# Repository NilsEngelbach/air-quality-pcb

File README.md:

# Air Quality Checker — PCB

Custom 2-layer KiCad boards for the [air-quality-checker](../air-quality-checker) firmware: a battery-powered
indoor air-quality monitor. A Bosch **BME688** measures the air, an **SG92R** micro servo points at the current IAQ
band, and readings can be uploaded over WiFi. A LiPo cell powers it and charges over USB-C. The device sleeps
~98 % of the time and wakes every 5 minutes.

The repo holds every board revision in its own folder. **The current board is [`v9/`](v9/) (rev I).**

---

## Current board — v9 (rev I)

| Block | Part | Notes |
|---|---|---|
| MCU | **ESP32-C3-WROOM-02-N4** | native USB Serial/JTAG (no USB-UART bridge), antenna in a board notch with no copper beside it |
| Sensor | **BME688** on-board, I²C 0x76 | on a slotted island at the board edge for thermal isolation |
| Indicator | **SG92R** servo header | from VSYS through a load switch (Q6): 0 µA in sleep, 4.5 V on USB / 3.0–4.2 V on battery |
| Charger | **MCP73831**, ~303 mA | charge status to the MCU (IO20) and a green side-view LED |
| Regulator | **AP2112K-3.3** | 600 mA LDO |
| Power path | DMG2305UX P-FETs + B5819W | USB priority, battery reverse-polarity protection, POWER switch drives a FET |
| Controls | POWER (SPDT) + **WiFi mode** (SP3T: OFF / SPARSE / CONTINUOUS) slide switches | right-angle, actuators through the enclosure wall |
| Indicators | blue STATUS + green CHG side-view LEDs | visible from the enclosure side |
| Expansion | **STEMMA QT / Qwiic** port | switched 3.3 V and bus isolation: 0 µA when off; e.g. for a real CO₂ sensor |
| Protection | 2 × USBLC6-2SC6 | USB data lines and the STEMMA QT port |
| Board | Ø 72 mm round, bottom flat for the controls, 2 layers, 1.6 mm FR4 | 0.3 mm minimum drill; assembled by PCBWay |

**State (2026-10-08):** layout done, ERC 0 / DRC 0 with schematic parity; schematic PDF and PCBWay BOM generated.
Gerbers, the ESP32-C3 firmware port and bench validation are still open.

| v9 document | For |
|---|---|
| [`v9/README.md`](v9/README.md) | changes vs v8, pin map, power architecture, firmware port, outputs, next steps |
| [`v9/user-documentation.md`](v9/user-documentation.md) | people using the device |
| [`v9/design_review.md`](v9/design_review.md) | findings F1–F34 with evidence and validation checklists |
| [`v9/layout_constraints.md`](v9/layout_constraints.md) | layout rules |
| [`v9/power_budget.md`](v9/power_budget.md) | sleep floor, wake budget, battery life per WiFi mode |

---

## Revisions

| Rev | Folder | Summary | Docs |
|---|---|---|---|
| A | [`v1/`](v1/) | 108 × 108 mm square. ESP-12F (ESP8266) + CP2102N, BME688 breakout over STEMMA QT, servo from VBAT | [README](v1/README.md) |
| B | [`v2/`](v2/) | Same circuit on a **Ø 72 mm round** board, mounting holes, wind logo | [README](v2/README.md) |
| C | [`v3/`](v3/) | **BME688 soldered on-board**, copper keep-out under the sensor | [README](v3/README.md) |
| D | [`v4/`](v4/) | GPIO2 status LED, battery sensing, USB ESD, battery reverse-polarity FET, spare-GPIO header, fiducials, **5 V servo boost** | [README](v4/README.md) |
| E | [`v5/`](v5/) | Production / assembly refresh (PCBWay BOM, replacement power switch); battery-life analysis | [power budget](v5/power_budget.md) |
| F | [`v6/`](v6/) | Gated servo boost, **3-position WiFi mode switch**, side-view status LED, MΩ battery divider | [README](v6/README.md), [user docs](v6/user-documentation.md), [power budget](v6/power_budget.md) |
| G | [`v7/`](v7/) | **ESP32-C3** (native USB, no CP2102N), FET-driven power switch, servo-rail load switch, long-actuator edge switches, STEMMA QT port, charge-status input, antenna notch and sensor island | [README](v7/README.md), [design review](v7/design_review.md) |
| H | [`v8/`](v8/) | **Servo boost removed** (servo from VSYS), Espressif WROOM-02 footprint so the board keeps the 0.3 mm minimum drill. Fabrication outputs were generated | [README](v8/README.md), [design review](v8/design_review.md) |
| I | [`v9/`](v9/) | Re-placed and re-routed v8: **GPIO remap**, LDO at the module, smaller sensor island, no copper beside the antenna, C24 on the STEMMA QT rail | [README](v9/README.md) and the documents above |

Each revision's README lists what changed against the one before. From v7 on, the design reviews number their
findings (F1, F2, …) and carry them forward, so a finding keeps its number across revisions.

---

## Repository layout

```
README.md                   this overview
build_pcbway_bom.py         KiCad BOM export → PCBWay BOM (python build_pcbway_bom.py v9)
a-sample-of-PCBWay-BOM.xlsx PCBWay's BOM template, the format the script produces
wind.svg                    wind logo used on the back silkscreen (v2+)
vN/
  air-quality-pcb-vN.kicad_pro / .kicad_sch / .kicad_pcb
  README.md, design_review.md, layout_constraints.md, power_budget.md, user-documentation.md   (as available)
  bom_kicad_raw.csv → bom_pcbway_vN.csv, schematic_vN.pdf                                       (as generated)
  Espressif.pretty/, SamacSys_Parts.pretty/, fp-lib-table, air-quality-pcb-vN.3dshapes/       (v7+: vendor footprints and STEP models)
```

Not in git (see `.gitignore`): `gerbers/`, `*.rpt` (ERC/DRC reports), KiCad backups and lock files. Regenerate
them with the `kicad-cli` commands in each revision's README (KiCad 10).

### PCBWay BOM

1. Export the schematic BOM ungrouped, with the fields `Reference,Value,Footprint,Manufacturer,MPN,Description`, to
   `vN/bom_kicad_raw.csv` (command in the revision README).
2. `python build_pcbway_bom.py vN` groups it into PCBWay's columns and writes `vN/bom_pcbway_vN.csv`.

---

## Firmware

The firmware lives in the sibling [`air-quality-checker`](../air-quality-checker) repo. It currently targets the
**ESP8266 boards (v1–v6)**. The ESP32-C3 boards (v7–v9) need a port: PlatformIO `espressif32`, ESP-IDF deep sleep,
the new pin map, BME688 at 0x76. The steps are in [`v7/README.md`](v7/README.md#firmware-port-air-quality-checker-repo),
with the servo rules from v8 and the **v9 pin map** in [`v9/README.md`](v9/README.md#firmware-port-air-quality-checker-repo).
The v7/v8 and v9 pin maps differ, so a v8 build must not be flashed onto a v9 board.

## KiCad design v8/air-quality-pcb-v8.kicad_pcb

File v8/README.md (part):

# Air Quality Checker — PCB v8 (rev H)

Eighth iteration, derived from the routed v7 board. Two changes: the **5 V servo boost is
gone** (the servo now runs from VSYS through the existing load switch), and the **board keeps
PCBWay's standard 0.3 mm minimum drill**: the ESP32-C3-WROOM-02 now uses Espressif's footprint, whose EPAD has no drills.

**State (2026-10-05): layout done, fabrication outputs exported.** Schematic ERC **0 errors / 0 warnings**
(`erc_v8.rpt`). Board DRC with schematic parity **0 errors, 0 unconnected** (`drc_v8.rpt`, also clean after a
zone refill); the only remaining warnings are 4 excluded silkscreen-clipped warnings (U1 at the antenna notch, J1 at the
bottom flat) and the 7 board-only footprints (H1–H4, FID1–3). Gerbers, drill, position file and the PCBWay
BOM are generated (see *Files*). What is left is the order itself and the bench validation. Rules:
[`layout_constraints.md`](layout_constraints.md); findings and validation checklists:
[`design_review.md`](design_review.md) (F1–F24 from v7, F25–F26 new).

For the v6 → v7 changes (ESP32-C3, CP2102N removal, switches, STEMMA QT, …) see [`../v7/README.md`](../v7/README.md).

---

## What changed vs v7

| # | Change | Why (finding) |
|---|---|---|
| 1 | **Boost removed:** U7 MT3608, L1 10 µH, D4 PMEG4030ER, C18 / C21 22 µF, R22 / R23 (feedback) | fewer parts; the servo runs from VSYS (F25) |
| 2 | **Servo rail = VSYS through Q6**: net `SERVO_PWR` (was BOOST_IN + SERVO_5V) = Q6 drain, C22, C19 22 µF, C13 100 µF, J3.2 | servo works on USB (≈ 4.5 V) and on battery (3.0–4.2 V); still 0 µA in sleep (F2, F25) |
| 3 | Nets renamed: **BOOST_EN → SERVO_EN** (IO10), BOOST_GATE → SERVO_GATE, BOOST_PD → SERVO_PD | no boost any more |
| 4 | **U1 footprint → `Espressif:ESP32-C3-WROOM-02`** (from [espressif/kicad-libraries](https://github.com/espressif/kicad-libraries), with STEP): EPAD = 9 pads, no drills | the stock footprint has 12 × 0.2 mm EPAD drills (F15, F26) |
| 5 | **4 GND vias 0.6 / 0.3 mm** in the EPAD gaps (tented); `min_through_hole_diameter` back to **0.3 mm** | PCBWay standard drill (F26) |
| 6 | Board rule area **ANTENNA_KEEPOUT** (28 × 11 mm, F.Cu + B.Cu) | Espressif's footprint only keeps out 18 × 6 mm; this keeps the stock footprint's larger keepout (F7, F26) |
| 7 | Net class **Power**: `/SERVO_5V` → `/SERVO_PWR`, `/BOOST_SW` dropped | (F5) |
| 8 | Title block / back silkscreen **rev H** | |
| 9 | **C19 moved** to (79.5, 49.5) next to C13/J3; SERVO_PWR runs Q6 → C22 → C19 → C13 → J3.2 on F.Cu, 0.8 mm, 25 mm | the boost output position no longer made sense (F25) |
| 10 | **GND stitching near the antenna:** a 15-via fence along the module's ground edge (y 27.5), a ~2.5 mm grid under the module, and vias on both sides of the antenna notch (the left side now has F.Cu pour) | Espressif layout guide: dense GND vias at the module and the antenna (F7) |
| 11 | Silkscreen pin labels **S / + / −** at the servo header J3 | J4 (LiPo) has none: the JST PH plug is keyed |

Everything else (power path, charger, LDO, STEMMA QT, switches, LEDs, outline, placement) is unchanged from v7.

## Pin map (ESP32-C3-WROOM-02)

| GPIO | Net | Function |
|---|---|---|
| IO0 | VBAT_SENSE | ADC1_CH0, divider 1 M / 270 k (4.2 V → 0.89 V, use 2.5 dB attenuation) |
| IO1 | VBUS_SENSE | ADC1_CH1, 5 V → 1.59 V (USB present) |
| IO2 | QT_PWR_N | **STEMMA QT power, active low** (strap pin, R2 10 k pull-up → port off at reset and in sleep) |
| IO3 | MODE_A | SW4 POS1 → LOW = WiFi **OFF** |
| IO4 | MODE_B | SW4 POS3 → LOW = **CONTINUOUS** (both HIGH = SPARSE) |
| IO5 | SERVO_PWM | servo signal via R17 |
| IO6 / IO7 | SDA / SCL | I²C: BME688 (**0x76**) + STEMMA QT port (through Q9/Q10) |
| IO8 | STATUS_LED_N | blue side LED D3, **active-low**; strap (10 k pull-up) |
| IO9 | BOOT | SW2, strap (10 k pull-up) |
| IO10 | **SERVO_EN** | HIGH = servo rail on (Q7 → Q6); R4 100 k pull-down keeps it off |
| IO18 / IO19 | USB D− / D+ | native USB Serial/JTAG |
| IO20 | CHG_DET | charger STAT via divider: LOW = charging (only valid with VBUS present), HIGH = done |
| IO21 | — | not connected (spare) |

## Power architecture

```
USB-C VBUS ─┬─► MCP73831 (303 mA) ─► VBAT_RAW ◄── Q4 (reverse-polarity) ◄── LiPo J4
            │        └─ STAT ─► D2 (green) / R31-R32 ─► IO20
            │                        │
            │                  Q5 (SW3 drives the gate)
            │                        ▼
            └─►|D1|──► VSYS ◄── Q3 (USB priority) ── VBAT
                        │
                        ├─► AP2112K-3.3 ─► +3V3 (ESP32-C3, BME688, LED) ─► Q8 (IO2) ─► QT_3V3 ─► J5
                        └─► Q6 (SERVO_EN via Q7) ─► SERVO_PWR (C19 22 µF + C13 100 µF) ─► J3
```

Servo supply: **≈ 4.5 V on USB** (VBUS − D1), **3.0–4.2 V on battery**. The SG92R is rated 4.8–6 V; on
battery it moves with less torque and speed (F25 — validate on the bench).

Sleep floor estimate unchanged: ≈ **66 µA** (ESP32-C3 5 µA + AP2112K 55 µA + VBAT divider 3.3 µA +
BME688 ~2 µA + R26 0.4 µA; servo rail and QT port 0). Measure before updating the battery tables.

## Firmware port (air-quality-checker repo)

As in [`../v7/README.md`](../v7/README.md#firmware-port-air-quality-checker-repo), with these servo changes:

- **IO10 is now `SERVO_EN`** (was BOOST_EN): drive it HIGH **≥ 50 ms before** a move (SERVO_PWR ramps at
  ~0.5 V/ms, ≈ 8 ms to VSYS), LOW again after the move and before deep sleep.
- **Skip or postpone servo moves when VBAT < ~3.5 V** on battery: the servo's start-up current can pull VSYS
  below the LDO's dropout and brown out the ESP32-C3 (F25).
- **Prefer moving the servo with WiFi off** (not during TX bursts). On a 500 mA USB 2.0 port, charger + WiFi + servo
  start can exceed the port budget.
- Never drive SERVO_PWM while SERVO_EN is LOW (it would back-feed the unpowered servo through R17).

## Files

| File | Purpose |
|---|---|
| `air-quality-pcb-v8.kicad_pro/.kicad_sch/.kicad_pcb` | v8 project (ERC clean; board DRC clean with parity) |
| `Espressif.pretty/`, `SamacSys_Parts.pretty/`, `fp-lib-table` | vendor footprints: U1 (Espressif) and SW4 (OS103011MA7QP1, Mouser / SamacSys) |
| `air-quality-pcb-v8.3dshapes/` | STEP models for the vendor footprints and the side LEDs |
| `design_review.md` | findings F1–F26 with evidence, sources and validation checklists |
| `layout_plan.md` | what changed on the board, and the remaining layout steps for v8 |
| `layout_constraints.md` | the rules: antenna, servo rail, edge overhang, widths |
| `schematic_v8.pdf` | plotted schematic |
| `erc_v8.rpt` / `drc_v8.rpt` | ERC (clean) / DRC with schematic parity (clean) |
| `gerbers/air-quality-pcb-v8-gerbers.zip` | **upload to PCBWay:** 9 Gerber layers + job file + drill file (Excellon, PTH and NPTH merged; smallest hole 0.30 mm) |
| `gerbers/` | the same files unzipped, plus `air-quality-pcb-v8-drl_map.pdf` and `air-quality-pcb-v8-pos.csv` (placement, mm, all top side: 71 parts + 3 fiducials) |
| `bom_kicad_raw.csv` → `bom_pcbway_v8.csv` | schematic BOM export → PCBWay BOM (38 lines, 71 placements; SW3, SW4, J3, J4 THT), built with `python build_pcbway_bom.py v8` |

### Regenerate outputs (run in `v8/`)

```sh
kicad-cli sch erc -o erc_v8.rpt air-quality-pcb-v8.kicad_sch
kicad-cli pcb drc --schematic-parity -o drc_v8.rpt air-quality-pcb-v8.kicad_pcb
kicad-cli pcb export gerbers -o gerbers/ --subtract-soldermask --check-zones \
  --layers "F.Cu,B.Cu,F.Paste,B.Paste,F.Silkscreen,B.Silkscreen,F.Mask,B.Mask,Edge.Cuts" air-quality-pcb-v8.kicad_pcb
kicad-cli pcb export drill -o gerbers/ --format excellon --generate-map --map-format pdf air-quality-pcb-v8.kicad_pcb
kicad-cli pcb export pos -o gerbers/air-quality-pcb-v8-pos.csv --format csv --units mm --side both air-quality-pcb-v8.kicad_pcb
kicad-cli sch export bom -o bom_kicad_raw.csv --fields "Reference,Value,Footprint,Manufacturer,MPN,Description" \
  --group-by "" air-quality-pcb-v8.kicad_sch
python ../build_pcbway_bom.py v8
```

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
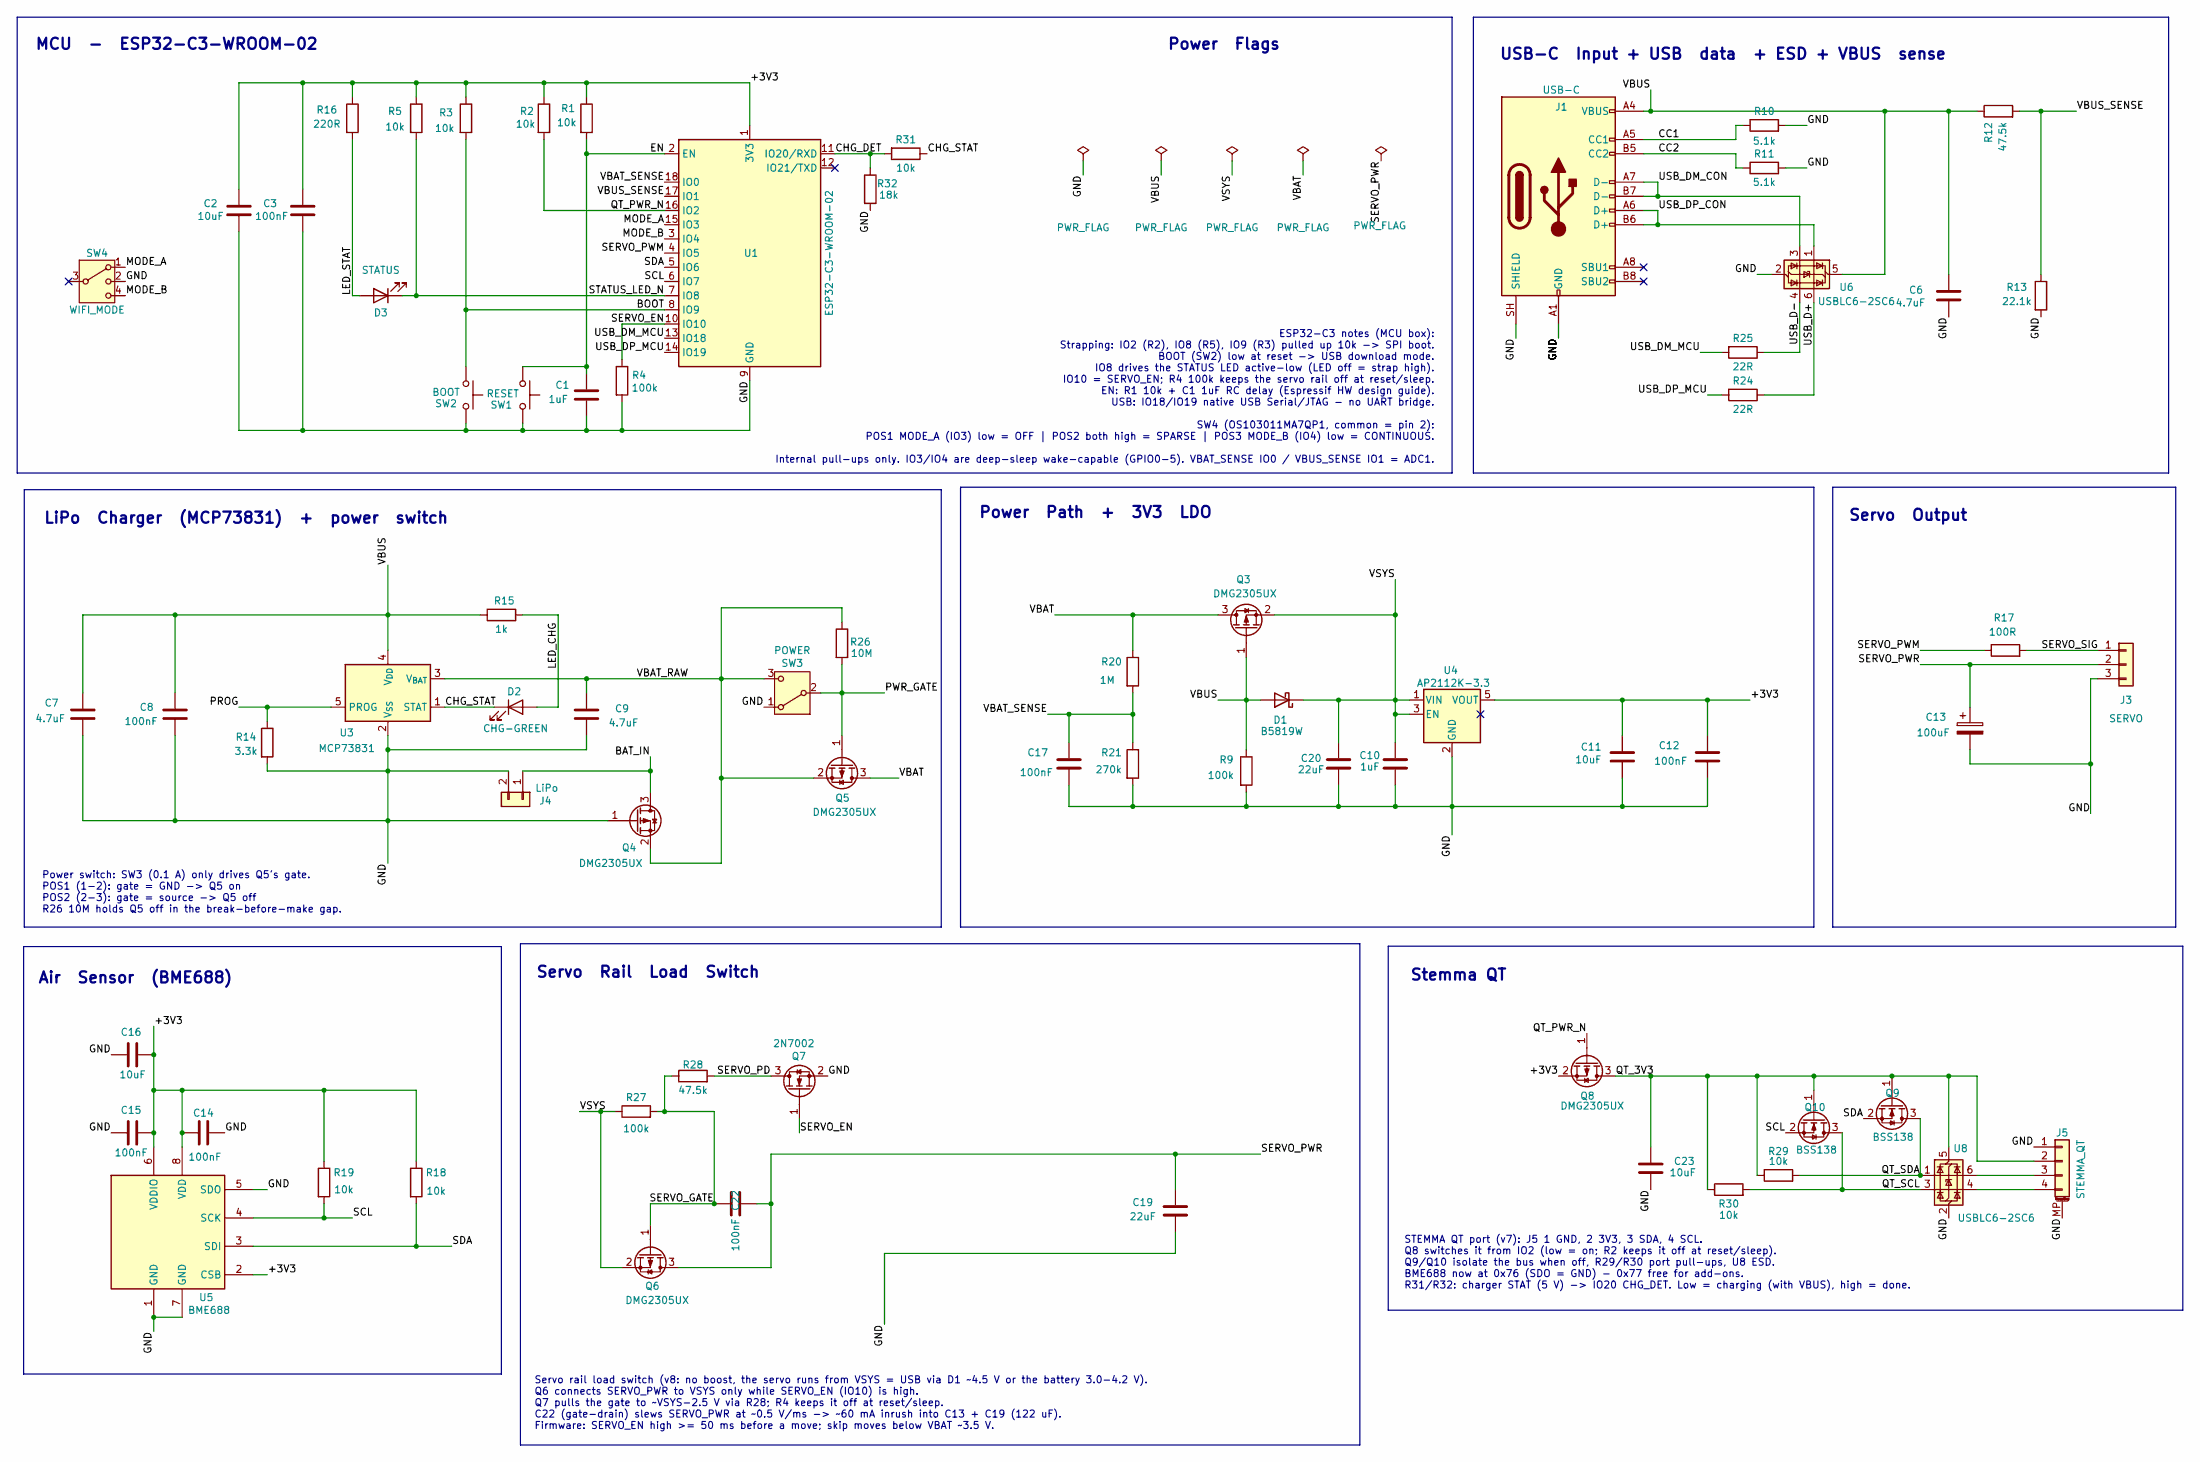
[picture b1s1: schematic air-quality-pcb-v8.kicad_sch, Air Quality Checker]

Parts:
C1, C10: 1uF; C_0805_2012Metric; MPN CL21B105KOFNNWE
C2, C11, C16, C23: 10uF; C_0805_2012Metric; MPN CC0805KRX5R7BB106
C3, C8, C12, C14, C15, C17, C22: 100nF; C_0805_2012Metric; MPN CL21B104KBCNNNC
C6, C7, C9: 4.7uF; C_0805_2012Metric; MPN CL21A475KOFNNNG
C13: 100uF; CP_Elec_6.3x5.4; MPN UCD1C101MCL1GS
C19, C20: 22uF; C_0805_2012Metric; MPN CL21A226KOQNNNG
D1: B5819W; D_SOD-123; MPN B5819W-TP
D2: CHG-GREEN; LED_Kingbright_KPA-3010_3x2x1mm; MPN KPA-3010SGC
D3: STATUS; LED_Kingbright_KPA-3010_3x2x1mm; MPN KPA-3010QBC-D
J1: USB-C; USB_C_Receptacle_HRO_TYPE-C-31-M-12; MPN TYPE-C-31-M-12
J3: SERVO; PinHeader_1x03_P2.54mm_Vertical; MPN 61300311121
J4: LiPo; JST_PH_B2B-PH-K_1x02_P2.00mm_Vertical; MPN B2B-PH-K-S
J5: STEMMA_QT; JST_SH_SM04B-SRSS-TB_1x04-1MP_P1.00mm_Horizontal; MPN SM04B-SRSS-TB(LF)(SN)
Q3, Q4, Q5, Q6, Q8: DMG2305UX; SOT-23; MPN DMG2305UX-7
Q7: 2N7002; SOT-23; MPN 2N7002-7-F
Q9, Q10: BSS138; SOT-23; MPN BSS138
R1, R2, R3, R5, R18, R19, R29, R30, R31: 10k; R_0805_2012Metric; MPN RC0805FR-0710KL
R4, R9, R27: 100k; R_0805_2012Metric; MPN RC0805FR-07100KL
R10, R11: 5.1k; R_0805_2012Metric; MPN RC0805FR-075K1L
R12, R28: 47.5k; R_0805_2012Metric; MPN RC0805FR-0747K5L
R13: 22.1k; R_0805_2012Metric; MPN RC0805FR-0722K1L
R14: 3.3k; R_0805_2012Metric; MPN RC0805FR-073K3L
R15: 1k; R_0805_2012Metric; MPN RC0805FR-071KL
R16: 220R; R_0805_2012Metric; MPN RC0805FR-07220RL
R17: 100R; R_0805_2012Metric; MPN RC0805FR-07100RL
R20: 1M; R_0805_2012Metric; MPN RC0805FR-071ML
R21: 270k; R_0805_2012Metric; MPN RC0805FR-07270KL
R24, R25: 22R; R_0805_2012Metric; MPN RC0805FR-0722RL
R26: 10M; R_0805_2012Metric; MPN RC0805FR-0710ML
R32: 18k; R_0805_2012Metric; MPN RC0805FR-0718KL
SW1: RESET; SW_Push_1P1T_NO_CK_KMR2; MPN KMR221G LFS
SW2: BOOT; SW_Push_1P1T_NO_CK_KMR2; MPN KMR221G LFS
SW3: POWER; SW_Slide_SPDT_Angled_CK_OS102011MA1Q; MPN OS102011MA1QN1
SW4: WIFI_MODE; OS103011MA7QP1; MPN OS103011MA7QP1
U1: ESP32-C3-WROOM-02; MPN ESP32-C3-WROOM-02-N4
U3: MCP73831; SOT-23-5; MPN MCP73831T-2ACI/OT
U4: AP2112K-3.3; SOT-23-5; MPN AP2112K-3.3TRG1
U5: BME688; Bosch_LGA-8_3x3mm_P0.8mm_ClockwisePinNumbering; MPN BME688
U6, U8: USBLC6-2SC6; SOT-23-6; MPN USBLC6-2SC6

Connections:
/+3V3: C2.1, C3.1, C11.1, C12.1, C14.1, C15.1, C16.1, Q8.2 (S), R1.1, R2.1, R3.1, R5.1, R16.1, R18.1, R19.1, U1.1 (3V3), U4.5 (VOUT), U5.2 (CSB), U5.6 (VDDIO), U5.8 (VDD)
/BAT_IN: J4.1, Q4.3 (D)
/BOOT: R3.2, SW2.1, U1.8 (IO9)
/CC1: J1.A5 (CC1), R10.1
/CC2: J1.B5 (CC2), R11.1
/CHG_DET: R31.2, R32.1, U1.11 (IO20/RXD)
/CHG_STAT: D2.1 (K), R31.1, U3.1 (STAT)
/EN: C1.1, R1.2, SW1.1, U1.2 (EN)
/GND: C1.2, C2.2, C3.2, C6.2, C7.2, C8.2, C9.2, C10.2, C11.2, C12.2, C13.2, C14.2, C15.2, C16.2, C17.2, C19.2, C20.2, C23.2, J1.A1 (GND), J1.A12 (GND), J1.B1 (GND), J1.B12 (GND), J1.SH (SHIELD), J3.3, J4.2, J5.1, J5.MP (MountPin), Q4.1 (G), Q7.2 (S), R4.2, R9.2, R10.2, R11.2, R13.2, R14.2, R21.2, R32.2, SW1.2, SW2.2, SW3.1 (A), SW4.2, U1.9 (GND), U1.19 (GND), U3.2 (V_{SS}), U4.2 (GND), U5.1 (GND), U5.5 (SDO), U5.7 (GND), U6.2 (GND), U8.2 (GND)
/LED_CHG: D2.2 (A), R15.2
/LED_STAT: D3.2 (A), R16.2
/MODE_A: SW4.1, U1.15 (IO3)
/MODE_B: SW4.4, U1.3 (IO4)
/PROG: R14.1, U3.5 (PROG)
/PWR_GATE: Q5.1 (G), R26.2, SW3.2 (B)
/QT_3V3: C23.1, J5.2, Q8.3 (D), Q9.1 (G), Q10.1 (G), R29.1, R30.1, U8.5 (VBUS)
/QT_PWR_N: Q8.1 (G), R2.2, U1.16 (IO2)
/QT_SCL: Q10.3 (D), R30.2, U8.3 (I/O2)
/QT_SDA: Q9.3 (D), R29.2, U8.1 (I/O1)
/SCL: Q10.2 (S), R19.2, U1.6 (IO7), U5.4 (SCK)
/SDA: Q9.2 (S), R18.2, U1.5 (IO6), U5.3 (SDI)
/SERVO_EN: Q7.1 (G), R4.1, U1.10 (IO10)
/SERVO_GATE: C22.2, Q6.1 (G), R27.2, R28.1
/SERVO_PD: Q7.3 (D), R28.2
/SERVO_PWM: R17.1, U1.4 (IO5)
/SERVO_PWR: C13.1, C19.1, C22.1, J3.2, Q6.3 (D)
/SERVO_SIG: J3.1, R17.2
/STATUS_LED_N: D3.1 (K), R5.2, U1.7 (IO8)
/USB_D+: R24.1, U6.6 (I/O1)
/USB_D-: R25.1, U6.4 (I/O2)
/USB_DM_CON: J1.A7 (D-), J1.B7 (D-), U6.3 (I/O2)
/USB_DM_MCU: R25.2, U1.13 (IO18)
/USB_DP_CON: J1.A6 (D+), J1.B6 (D+), U6.1 (I/O1)
/USB_DP_MCU: R24.2, U1.14 (IO19)
/VBAT: Q3.3 (D), Q5.3 (D), R20.1
/VBAT_RAW: C9.1, Q4.2 (S), Q5.2 (S), R26.1, SW3.3 (C), U3.3 (V_{BAT})
/VBAT_SENSE: C17.1, R20.2, R21.1, U1.18 (IO0)
/VBUS: C6.1, C7.1, C8.1, D1.2 (A), J1.A4 (VBUS), J1.A9 (VBUS), J1.B4 (VBUS), J1.B9 (VBUS), Q3.1 (G), R9.1, R12.1, R15.1, U3.4 (V_{DD}), U6.5 (VBUS)
/VBUS_SENSE: R12.2, R13.1, U1.17 (IO1)
/VSYS: C10.1, C20.1, D1.1 (K), Q3.2 (S), Q6.2 (S), R27.1, U4.1 (VIN), U4.3 (EN)
unnamed: J5.3, U8.6 (I/O1)
unnamed: J5.4, U8.4 (I/O2)

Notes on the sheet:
MCU - ESP32-C3-WROOM-02
Servo rail load switch (v8: no boost, the servo runs from VSYS = USB via D1 ~4.5 V or the battery 3.0-4.2 V). Q6 connects SERVO_PWR to VSYS only while SERVO_EN (IO10) is high. Q7 pulls the gate to ~VSYS-2.5 V via R28; R4 keeps it off at reset/sleep. C22 (gate-drain) slews SERVO_PWR at ~0.5 V/ms -> 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
STEMMA QT port (v7): J5 1 GND, 2 3V3, 3 SDA, 4 SCL. Q8 switches it from IO2 (low = on; R2 keeps it off at reset/sleep). Q9/Q10 isolate the bus when off, R29/R30 port pull-ups, U8 ESD. BME688 now at 0x76 (SDO = GND) - 0x77 free for add-ons. R31/R32: charger STAT (5 V) -> IO20 CHG_DET. Low = charging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
Power Path + 3V3 LDO
Power switch: SW3 (0.1 A) only drives Q5's gate. POS1 (1-2): gate = GND -> Q5 on POS2 (2-3): gate = source -> Q5 off R26 10M holds Q5 off in the break-before-make gap.
ESP32-C3 notes (MCU box): Strapping: IO2 (R2), IO8 (R5), IO9 (R3) pulled up 10k -> SPI boot. BOOT (SW2) low at reset -> USB download mode. IO8 drives the STATUS LED active-low (LED off = strap high). IO10 = SERVO_EN; R4 100k keeps the servo rail off at reset/sleep. EN: R1 10k + C1 1uF RC delay (Esp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
Air Sensor (BME688)
Power Flags
Stemma QT
USB-C Input + USB data + ESD + VBUS sense
LiPo Charger (MCP73831) + power switch
Servo Rail Load Switch
Servo Output

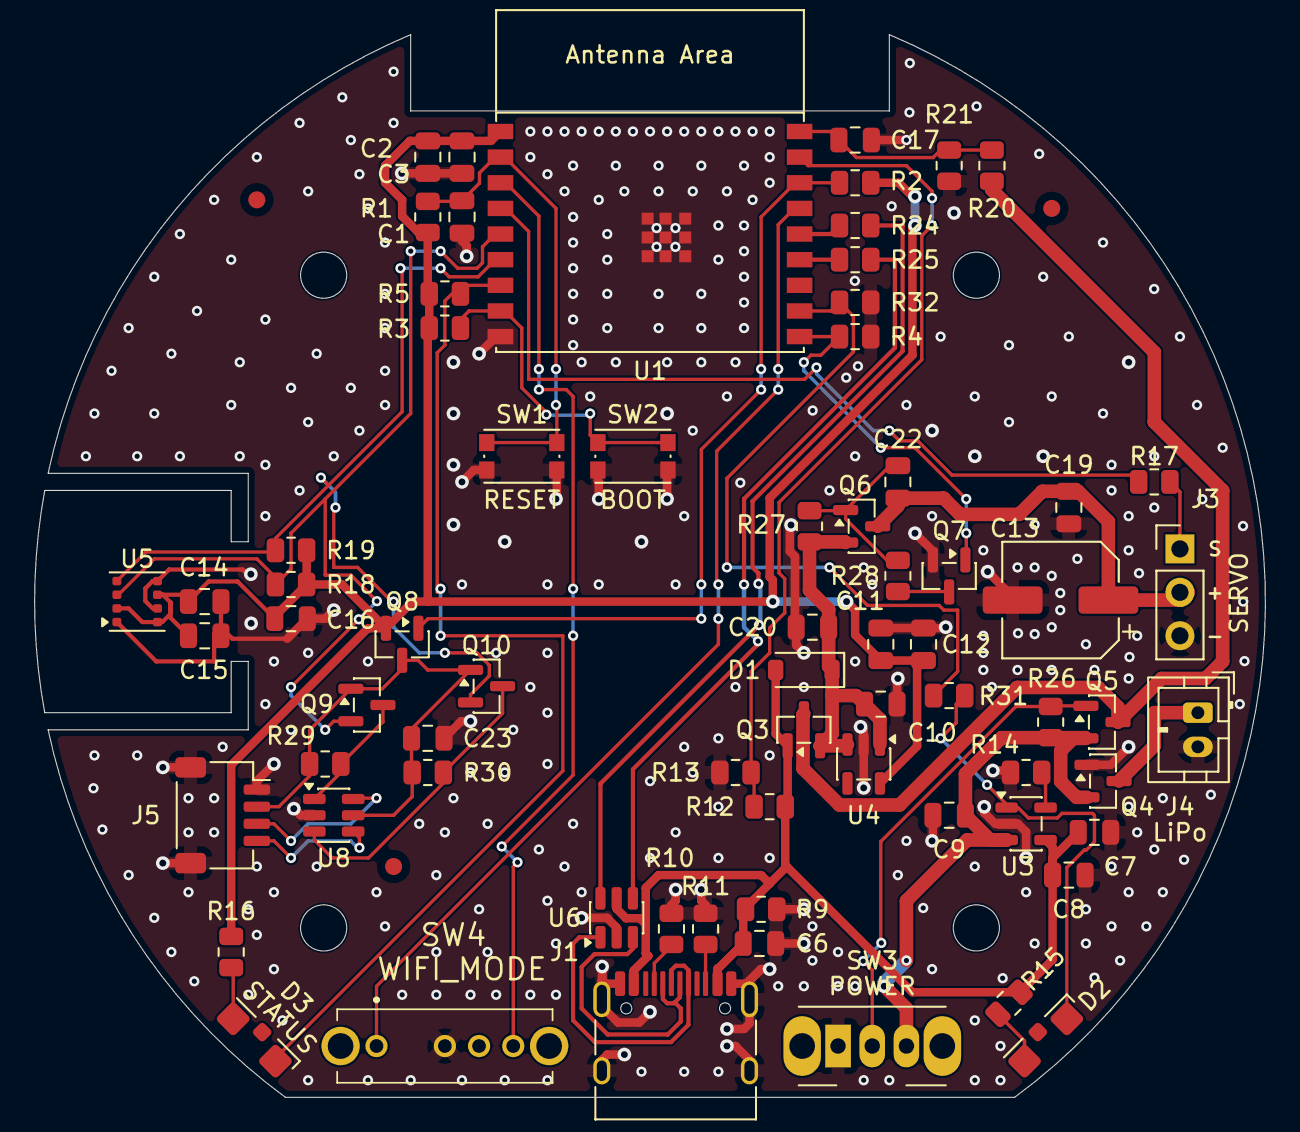
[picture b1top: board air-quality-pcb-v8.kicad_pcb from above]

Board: 2 copper layers, 72.0 x 62.2 mm, 78 parts (0 on the bottom side), 42 nets.

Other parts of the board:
FID1, FID2, FID3: Fiducial; Fiducial_1mm_Mask2mm
H1, H2, H3, H4: M2.5; MountingHole_2.7mm_M2.5

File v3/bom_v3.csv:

"Refs","Value","Footprint","Qty","DNP"
"C1","100nF","Capacitor_SMD:C_0805_2012Metric","1",""
"C2","10uF","Capacitor_SMD:C_0805_2012Metric","1",""
"C3","100nF","Capacitor_SMD:C_0805_2012Metric","1",""
"C4","4.7uF","Capacitor_SMD:C_0805_2012Metric","1",""
"C5","100nF","Capacitor_SMD:C_0805_2012Metric","1",""
"C6","4.7uF","Capacitor_SMD:C_0805_2012Metric","1",""
"C7","4.7uF","Capacitor_SMD:C_0805_2012Metric","1",""
"C8","100nF","Capacitor_SMD:C_0805_2012Metric","1",""
"C9","4.7uF","Capacitor_SMD:C_0805_2012Metric","1",""
"C10","1uF","Capacitor_SMD:C_0805_2012Metric","1",""
"C11","10uF","Capacitor_SMD:C_0805_2012Metric","1",""
"C12","100nF","Capacitor_SMD:C_0805_2012Metric","1",""
"C13","100uF","Capacitor_SMD:CP_Elec_6.3x5.4","1",""
"C14","100nF","Capacitor_SMD:C_0805_2012Metric","1",""
"C15","100nF","Capacitor_SMD:C_0805_2012Metric","1",""
"C16","10uF","Capacitor_SMD:C_0805_2012Metric","1",""
"D1","B5819W","Diode_SMD:D_SOD-123","1",""
"D2","CHG-GREEN","LED_SMD:LED_0805_2012Metric","1",""
"D3","PWR-RED","LED_SMD:LED_0805_2012Metric","1",""
"J1","USB-C","Connector_USB:USB_C_Receptacle_HRO_TYPE-C-31-M-12","1",""
"J3","SERVO","Connector_PinHeader_2.54mm:PinHeader_1x03_P2.54mm_Vertical","1",""
"J4","LiPo","Connector_JST:JST_PH_B2B-PH-SM4-TB_1x02-1MP_P2.00mm_Vertical","1",""
"JP1","DEEPSLEEP","Jumper:SolderJumper-2_P1.3mm_Bridged_Pad1.0x1.5mm","1",""
"Q1","MMBT2222A","Package_TO_SOT_SMD:SOT-23","1",""
"Q2","MMBT2222A","Package_TO_SOT_SMD:SOT-23","1",""
"Q3","DMG2305UX","Package_TO_SOT_SMD:SOT-23","1",""
"R1","10k","Resistor_SMD:R_0805_2012Metric","1",""
"R2","10k","Resistor_SMD:R_0805_2012Metric","1",""
"R3","10k","Resistor_SMD:R_0805_2012Metric","1",""
"R4","10k","Resistor_SMD:R_0805_2012Metric","1",""
"R5","10k","Resistor_SMD:R_0805_2012Metric","1",""
"R6","10k","Resistor_SMD:R_0805_2012Metric","1",""
"R7","10k","Resistor_SMD:R_0805_2012Metric","1",""
"R9","100k","Resistor_SMD:R_0805_2012Metric","1",""
"R10","5.1k","Resistor_SMD:R_0805_2012Metric","1",""
"R11","5.1k","Resistor_SMD:R_0805_2012Metric","1",""
"R12","22.1k","Resistor_SMD:R_0805_2012Metric","1",""
"R13","47.5k","Resistor_SMD:R_0805_2012Metric","1",""
"R14","2.2k","Resistor_SMD:R_0805_2012Metric","1",""
"R15","1k","Resistor_SMD:R_0805_2012Metric","1",""
"R16","1k","Resistor_SMD:R_0805_2012Metric","1",""
"R17","100R","Resistor_SMD:R_0805_2012Metric","1",""
"R18","10k","Resistor_SMD:R_0805_2012Metric","1",""
"R19","10k","Resistor_SMD:R_0805_2012Metric","1",""
"SW1","RESET","Button_Switch_SMD:SW_Push_1P1T_XKB_TS-1187A","1",""
"SW2","BOOT","Button_Switch_SMD:SW_Push_1P1T_XKB_TS-1187A","1",""
"SW3","POWER","Button_Switch_SMD:SW_SPDT_Shouhan_MSK12C02","1",""
"U1","ESP-12F","RF_Module:ESP-12E","1",""
"U2","CP2102N-A02-GQFN28","Package_DFN_QFN:QFN-28-1EP_5x5mm_P0.5mm_EP3.35x3.35mm","1",""
"U3","MCP73831","Package_TO_SOT_SMD:SOT-23-5","1",""
"U4","AP2112K-3.3","Package_TO_SOT_SMD:SOT-23-5","1",""
"U5","BME688","Package_LGA:Bosch_LGA-8_3x3mm_P0.8mm_ClockwisePinNumbering","1",""

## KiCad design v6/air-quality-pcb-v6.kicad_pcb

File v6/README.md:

# Air Quality Checker — PCB v6

Sixth iteration: the v5 board plus the **power-budget fixes**, a **3-position
WiFi mode switch**, and a **side-view status LED**. The layout has been
F8-synced and updated: SW4 + D3 placed, re-routed, zones refilled — DRC clean
(`drc_v6_check.rpt`). Gerbers are still to be generated.

> Baseline: v5 (round Ø 72 mm, on-board BME688, ESP-12F, CP2102N, MCP73831,
> AP2112K, MT3608 servo boost). See [`v5/power_budget.md`](../v5/power_budget.md)
> for the findings that motivated this revision, and [`power_budget.md`](power_budget.md)
> for the v6 numbers per WiFi mode.

---

## What changed vs v5

| # | Change | Why |
|---|---|---|
| 1 | **MT3608 EN (U7-4) driven by GPIO15** instead of VSYS | v5 kept the boost + SG92R alive 24/7 (~170 mAh/day — five times everything else). GPIO15's existing R4 10 kΩ pull-down holds EN low at boot and during deep sleep; MT3608 shutdown < 1 µA |
| 2 | **SW4: 3-position slide switch** (PCM13SMTR, SP3T ON-ON-ON) selects the WiFi mode | user-selectable OFF / SPARSE / CONTINUOUS without reflashing |
| 3 | **D3 → Kingbright KPA-3010QBC-D** side-view (right-angle) blue LED, R16 1 kΩ → **220 Ω** | LED must face out of the enclosure side; on 3.3 V a blue InGaN LED (Vf ≈ 2.8–3.0 V) barely conducts through 1 kΩ — 220 Ω gives ~2 mA |
| 4 | **VBAT_SENSE divider 100 k/27 k → 1 M/270 k** (R20/R21) | 29 µA → 3.3 µA continuous; same ratio (4.2 V → 0.89 V), C17 100 nF covers the ADC sampling |

No other nets touched. ERC: **0 errors, 0 warnings** (`erc_v6.rpt`).

---

## 1. WiFi mode switch (SW4)

C&K **PCM13SMTR**, SP3T ON-ON-ON right-angle slide switch
(`Button_Switch_SMD:SW_SP3T_PCM13`). Datasheet truth table (terminal 3 = common):

| Slide position | Connected terminals | v6 wiring | Firmware decode (INPUT_PULLUP) |
|---|---|---|---|
| POS.1 | 1–3 | pad 1 → **GPIO12** | GPIO12 = LOW → **WiFi OFF** |
| POS.2 | 2–3 | pad 2 → NC (no-connect) | both HIGH → **SPARSE** (upload 1×/hour) |
| POS.3 | 3–4 | pad 4 → **GPIO14** | GPIO14 = LOW → **CONTINUOUS** (upload every 5-min sample) |

Common (pad 3) → **GND**. Deliberately **no external pull-ups**: the pins are
read once at boot with the ESP8266 internal pull-ups; +3V3 stays alive in deep
sleep, so an external pull-up across a closed contact would leak ~330 µA 24/7.

Layout order on the slider is POS.1–POS.2–POS.3, i.e. **OFF – SPARSE –
CONTINUOUS** left to right when oriented like the schematic.

## 2. Servo boost gating (GPIO15)

Firmware contract: drive GPIO15 HIGH ≥ 100 ms before moving the servo, LOW
immediately after, never HIGH across a deep sleep. GPIO15 is a boot-strap pin —
R4 keeps it LOW at boot, which is exactly the required default (boost off).

## 3. Side-view status LED (D3)

Kingbright **KPA-3010QBC-D** (blue, right-angle, 3.0×2.0×1.0 mm), same circuit:
`+3V3 → R16 220 Ω → D3 → GPIO2`, active-LOW. Place it at the **board edge,
facing outward**. Pad 3 of the footprint is a mechanical dummy pad (stays
unconnected); verify polarity on the first board (pad 1 = cathode per the
Kingbright/KiCad pairing).

### LED behavior spec

| State | Pattern |
|---|---|
| Normal, IAQ accuracy ≥ 1 | solid ON while awake, OFF in deep sleep (as today) |
| Normal, accuracy = 0 (stabilizing) | 500 ms blink (as today) |
| **WiFi setup mode active** | **long – short – short** (600 ms ON, 200 ms OFF, 200 ms ON, 200 ms OFF, 200 ms ON, 1 s OFF, repeat) |
| WiFi OK (credentials found, normal upload) | no setup blinking; LED follows normal status |

## 4. WiFi credentials — setup flow (no flashing)

Credentials are **never compiled in**. At every boot where the mode switch is
SPARSE or CONTINUOUS:

1. Firmware checks for stored credentials (ESP8266 SDK flash sector /
   `WiFi.SSID()` non-empty, plus API config in LittleFS).
2. **Credentials present** → connect and upload (sparse: batch from LittleFS);
   LED shows normal status.
3. **No credentials** → enter **setup mode**: start captive-portal AP
   `Birdy-Setup-<chipid>` (WiFiManager or minimal custom AP+form), blink
   *long–short–short* so the user sees setup is waiting. User joins with a
   phone, enters SSID/password (+ API URL/key), device stores them in flash
   and reboots into the selected mode.
4. Setup timeout (~3 min) → back to deep sleep to protect the battery.
5. Re-provisioning later: hold **BOOT** (SW2) during RESET → forces setup mode
   regardless of stored credentials.

Stored credentials survive normal firmware flashes (SDK sector + LittleFS are
only wiped by a full flash erase). Energy cost of a setup session: ~15–20 mAh —
do first-time setup on USB power.

## 5. Power summary (details: [`power_budget.md`](power_budget.md))

Sleep floor **~80 µA** (was ~7.2 mA on v5 with the servo rail ungated).
Sizing at nameplate × 0.75:

| Mode | Daily | 30 days | 60 days | 90 days |
|---|---|---|---|---|
| OFF | ~34 mAh | 2000 mAh | 1× 18650 | 5000 mAh / 2× 18650 |
| SPARSE 1/h | ~38 mAh | 2000 mAh | 1× 18650 (3500) | 5000–6000 mAh / 2× 18650 |
| CONTINUOUS | ~75–90 mAh | 5000 mAh | 10 Ah / 3× 18650 | 4× 18650 — better: USB power |

---

## Schematic ↔ firmware pin map (delta vs v5)

| Net | ESP-12F pin | Function |
|---|---|---|
| `GPIO12` | GPIO12 | WiFi mode bit 0 (SW4 POS.1, LOW = OFF) |
| `GPIO14` | GPIO14 | WiFi mode bit 1 (SW4 POS.3, LOW = CONTINUOUS) |
| `GPIO15` | GPIO15 | **MT3608 enable** (boost for servo), was tied to VSYS |

Everything else unchanged (SDA/SCL GPIO4/5, SERVO_PWM GPIO13, LED GPIO2,
GPIO16→RST via JP1, VBAT_SENSE on ADC).

## Open work (not in this revision)

- **Gerbers**: layout is done (SW4 near SW3 at the board edge, D3 at the edge
  facing out; routed + refilled per repo `AGENTS.md`, DRC clean) — fabrication
  outputs not yet generated.
- **Firmware**: ✅ implemented in the `air-quality-checker` repo — SW4 mode
  decode at boot (`BirdyMode`), sparse-mode LittleFS buffering
  (`rtcData.bootCount % 12`, `BirdyStore`), setup-mode captive portal
  (`BirdySetup`, `Birdy-Setup-<chipid>`, ~3 min timeout), LED
  *long–short–short* pattern (`BirdyLED::setSetupPattern`), BOOST_EN gating
  around `birdyServo.setIaq()` (GPIO15, `BirdyServo`), and battery-voltage
  reading (`BirdyBattery`, VBAT_SENSE divider → ADC, uploaded as nullable
  `battery` column — apply dashboard migration `009_battery_voltage.sql`
  before flashing). Credentials are provisioned via the portal, never
  compiled in (`BirdyConfig`). Builds clean for `huzzah` + `huzzah_debug`.

## Files

| File | Purpose |
|---|---|
| `air-quality-pcb-v6.kicad_pro/.kicad_sch` | Project + schematic (ERC clean) |
| `air-quality-pcb-v6.kicad_pcb` | v6 layout: synced, SW4 + D3 placed, routed, zones refilled |
| `drc_v6_check.rpt` | DRC report: 0 violations |
| `power_budget.md` | v6 power analysis per WiFi mode |
| `user-documentation.md` | End-user guide: controls, LEDs, WiFi modes, setup, troubleshooting |
| `schematic_v6.pdf` | Plotted schematic |
| `bom_kicad_raw.csv` / `bom_pcbway_v6.csv` | BOM (raw / PCBWay assembly format) |
| `erc_v6.rpt` | ERC report: 0 violations |

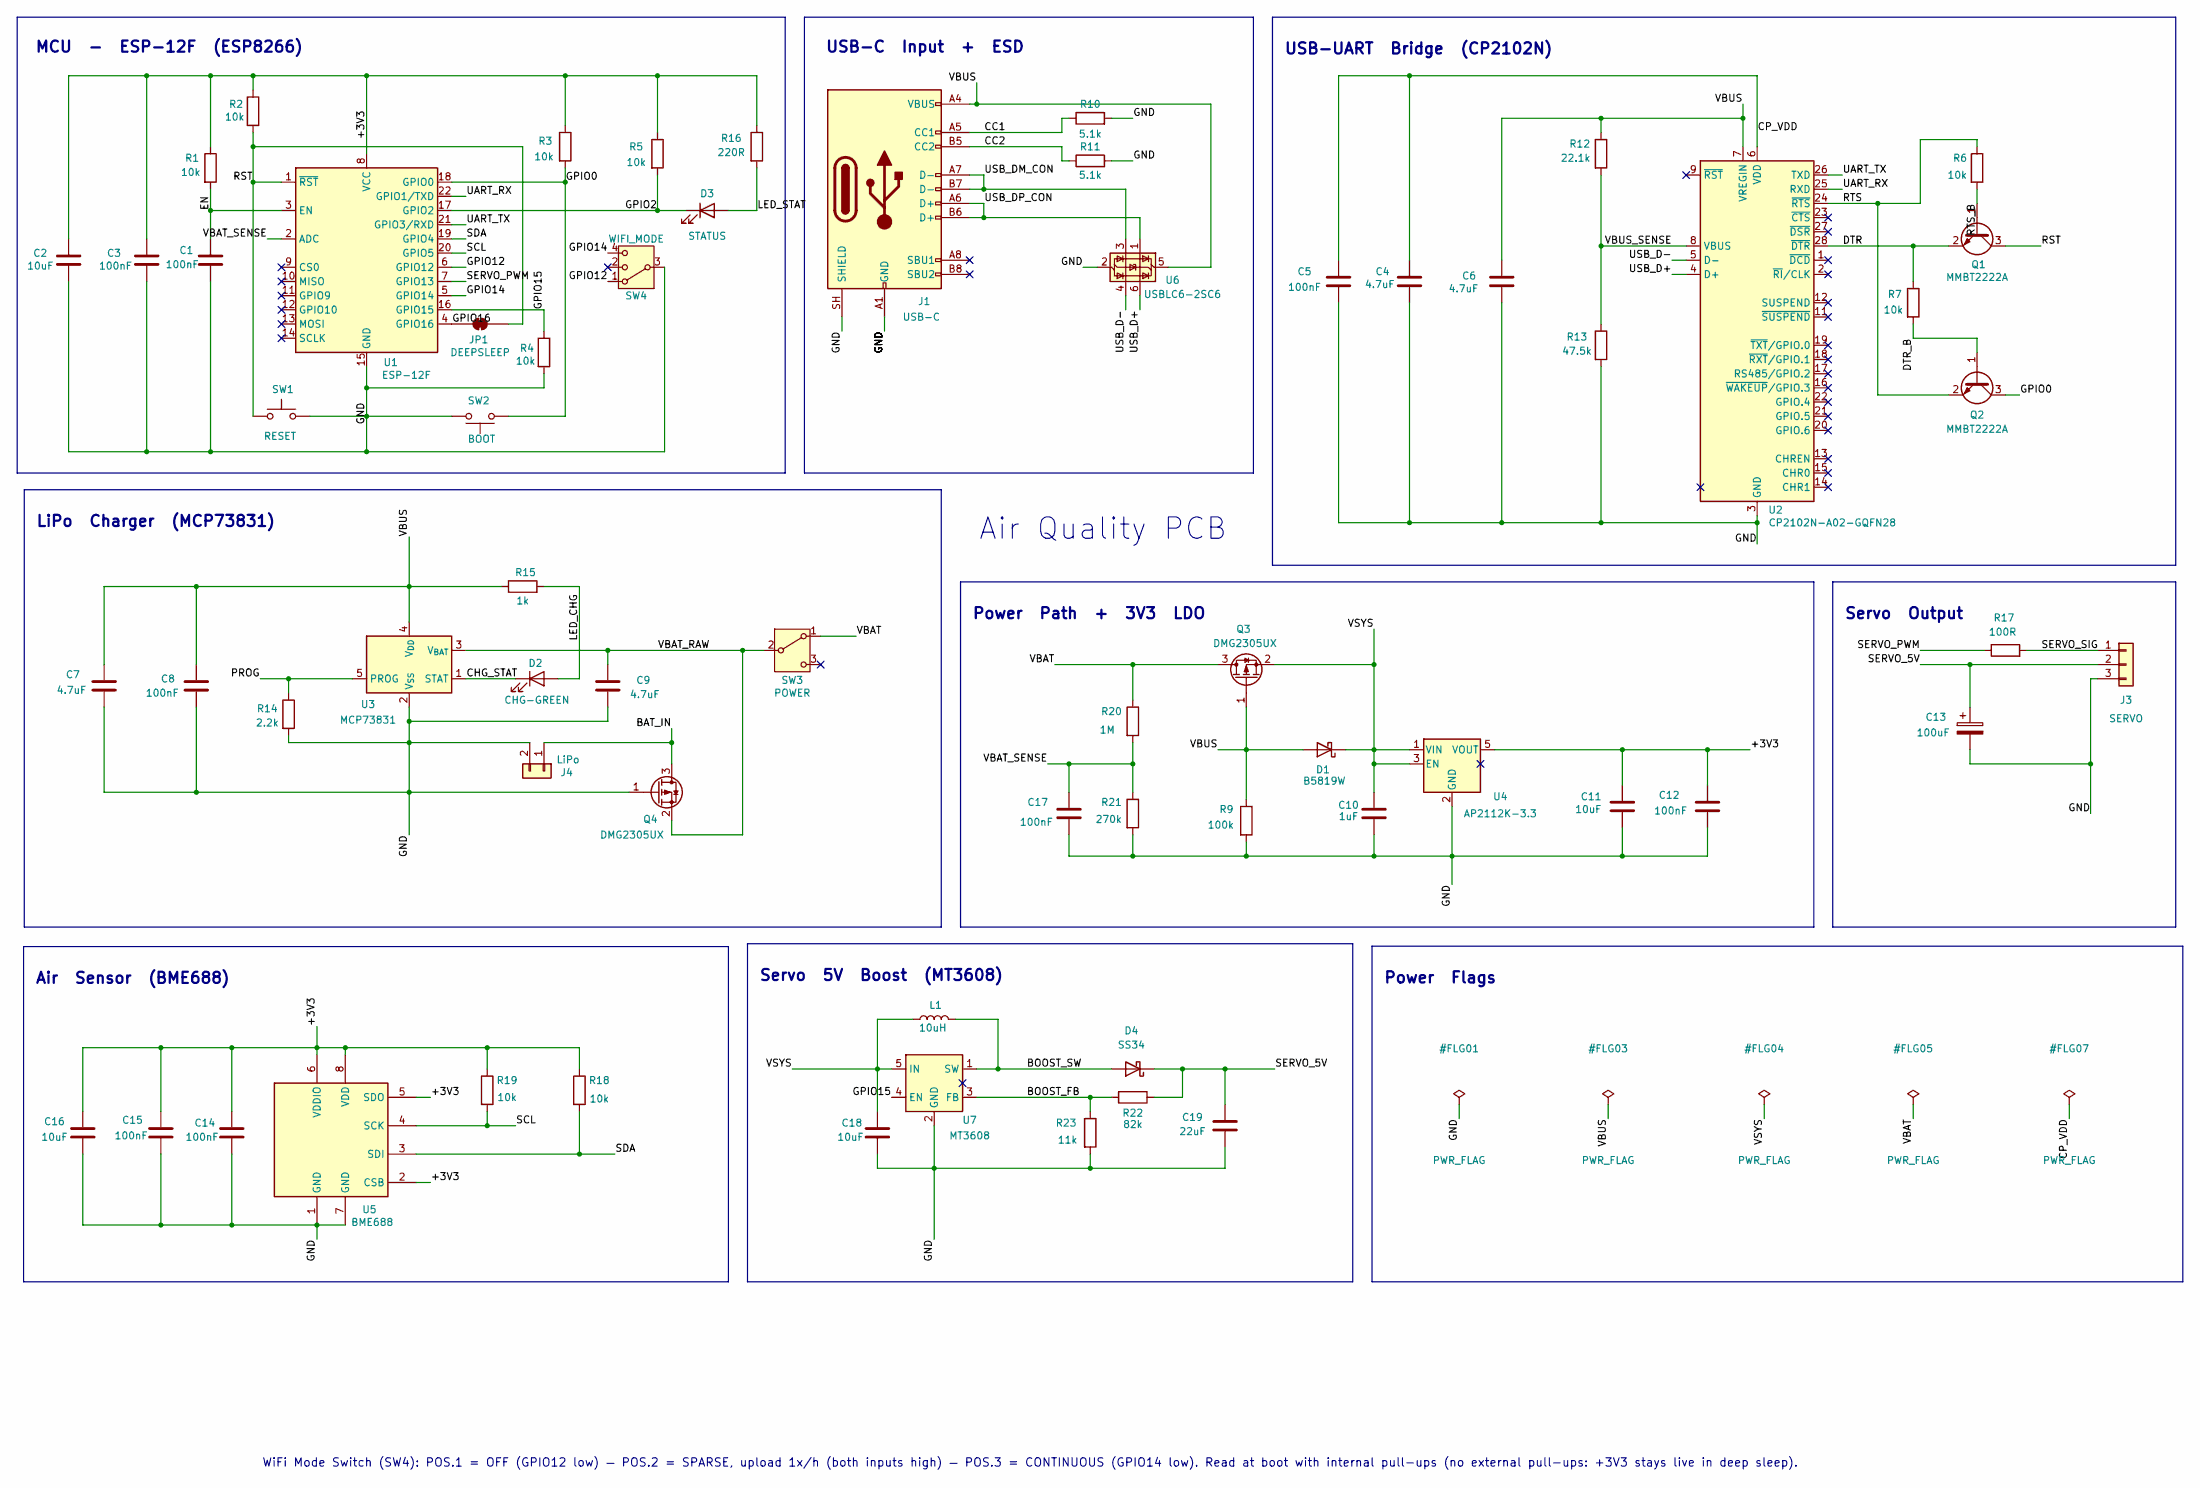
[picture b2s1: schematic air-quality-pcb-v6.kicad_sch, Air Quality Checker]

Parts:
C1, C3, C5, C8, C12, C14, C15, C17: 100nF; C_0805_2012Metric; MPN CL21B104KBCNNNC
C2, C11, C16, C18: 10uF; C_0805_2012Metric; MPN CC0805KRX5R7BB106
C4, C6, C7, C9: 4.7uF; C_0805_2012Metric; MPN CL21A475KOFNNNG
C10: 1uF; C_0805_2012Metric; MPN CL21B105KOFNNWE
C13: 100uF; CP_Elec_6.3x5.4; MPN UCD1C101MCL1GS
C19: 22uF; C_0805_2012Metric; MPN CL21A226KOQNNNG
D1: B5819W; D_SOD-123; MPN B5819W-TP
D2: CHG-GREEN; LED_0805_2012Metric; MPN LTST-C170GKT
D3: STATUS; LED_Kingbright_KPA-3010_3x2x1mm; MPN KPA-3010QBC-D
D4: SS34; D_SMA; MPN SS34-HF
J1: USB-C; USB_C_Receptacle_HRO_TYPE-C-31-M-12; MPN TYPE-C-31-M-12
J3: SERVO; PinHeader_1x03_P2.54mm_Vertical; MPN 61300311121
J4: LiPo; JST_PH_B2B-PH-K_1x02_P2.00mm_Vertical; MPN B2B-PH-K-S
JP1: DEEPSLEEP; SolderJumper-2_P1.3mm_Bridged_Pad1.0x1.5mm
L1: 10uH; L_Sunlord_SWPA4030S; MPN SWPA4030S100MT
Q1, Q2: MMBT2222A; SOT-23; MPN MMBT2222ALT1G
Q3, Q4: DMG2305UX; SOT-23; MPN DMG2305UX-7
R1, R2, R3, R4, R5, R6, R7, R18, R19: 10k; R_0805_2012Metric; MPN RC0805FR-0710KL
R9: 100k; R_0805_2012Metric; MPN RC0805FR-07100KL
R10, R11: 5.1k; R_0805_2012Metric; MPN RC0805FR-075K1L
R12: 22.1k; R_0805_2012Metric; MPN RC0805FR-0722K1L
R13: 47.5k; R_0805_2012Metric; MPN RC0805FR-0747K5L
R14: 2.2k; R_0805_2012Metric; MPN RC0805FR-072K2L
R15: 1k; R_0805_2012Metric; MPN RC0805FR-071KL
R16: 220R; R_0805_2012Metric; MPN RC0805FR-07220RL
R17: 100R; R_0805_2012Metric; MPN RC0805FR-07100RL
R20: 1M; R_0805_2012Metric; MPN RC0805FR-071ML
R21: 270k; R_0805_2012Metric; MPN RC0805FR-07270KL
R22: 82k; R_0805_2012Metric; MPN RC0805FR-0782KL
R23: 11k; R_0805_2012Metric; MPN RC0805FR-0711KL
SW1: RESET; SW_Push_1P1T_NO_CK_KMR2; MPN KMR221G LFS
SW2: BOOT; SW_Push_1P1T_NO_CK_KMR2; MPN KMR221G LFS
SW3: POWER; SW_SPDT_PCM12; MPN PCM12SMTBR
SW4: WIFI_MODE; SW_SP3T_PCM13; MPN PCM13SMTR
U1: ESP-12F; ESP-12E; MPN ESP-12F
U2: CP2102N-A02-GQFN28; QFN-28-1EP_5x5mm_P0.5mm_EP3.35x3.35mm; MPN CP2102N-A02-GQFN28
U3: MCP73831; SOT-23-5; MPN MCP73831T-2ACI/OT
U4: AP2112K-3.3; SOT-23-5; MPN AP2112K-3.3TRG1
U5: BME688; Bosch_LGA-8_3x3mm_P0.8mm_ClockwisePinNumbering; MPN BME688
U6: USBLC6-2SC6; SOT-23-6; MPN USBLC6-2SC6
U7: MT3608; SOT-23-6; MPN MT3608

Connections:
/+3V3: C2.1, C3.1, C11.1, C12.1, C14.1, C15.1, C16.1, R1.1, R2.1, R3.1, R5.1, R16.1, R18.1, R19.1, U1.8 (VCC), U4.5 (VOUT), U5.2 (CSB), U5.5 (SDO), U5.6 (VDDIO), U5.8 (VDD)
/BAT_IN: J4.1, Q4.3 (D)
/BOOST_FB: R22.2, R23.1, U7.3 (FB)
/BOOST_SW: D4.2 (A), L1.2, U7.1 (SW)
/CC1: J1.A5 (CC1), R10.1
/CC2: J1.B5 (CC2), R11.1
/CHG_STAT: D2.1 (K), U3.1 (STAT)
/CP_VDD: C4.1, C5.1, U2.6 (VDD)
/DTR: Q1.2 (E), R7.1, U2.28 (~DTR)
/DTR_B: Q2.1 (B), R7.2
/EN: C1.1, R1.2, U1.3 (EN)
/GND: C1.2, C2.2, C3.2, C4.2, C5.2, C6.2, C7.2, C8.2, C9.2, C10.2, C11.2, C12.2, C13.2, C14.2, C15.2, C16.2, C17.2, C18.2, C19.2, J1.A1 (GND), J1.A12 (GND), J1.B1 (GND), J1.B12 (GND), J1.SH (SHIELD), J3.3, J4.2, Q4.1 (G), R4.2, R9.2, R10.2, R11.2, R13.2, R14.2, R21.2, R23.2, SW1.2, SW2.2, SW4.3, U1.15 (GND), U2.3 (GND), U2.29 (GND), U3.2 (V_{SS}), U4.2 (GND), U5.1 (GND), U5.7 (GND), U6.2 (GND), U7.2 (GND)
/GPIO0: Q2.3 (C), R3.2, SW2.1, U1.18 (GPIO0)
/GPIO2: D3.1 (K), R5.2, U1.17 (GPIO2)
/GPIO12: SW4.1, U1.6 (GPIO12)
/GPIO14: SW4.4, U1.5 (GPIO14)
/GPIO15: R4.1, U1.16 (GPIO15), U7.4 (EN)
/GPIO16: JP1.1 (A), U1.4 (GPIO16)
/LED_CHG: D2.2 (A), R15.2
/LED_STAT: D3.2 (A), R16.2
/PROG: R14.1, U3.5 (PROG)
/RST: JP1.2 (B), Q1.3 (C), R2.2, SW1.1, U1.1 (~RST)
/RTS: Q2.2 (E), R6.1, U2.24 (~RTS)
/RTS_B: Q1.1 (B), R6.2
/SCL: R19.2, U1.20 (GPIO5), U5.4 (SCK)
/SDA: R18.2, U1.19 (GPIO4), U5.3 (SDI)
/SERVO_5V: C13.1, C19.1, D4.1 (K), J3.2, R22.1
/SERVO_PWM: R17.1, U1.7 (GPIO13)
/SERVO_SIG: J3.1, R17.2
/UART_RX: U1.22 (GPIO1/TXD), U2.25 (RXD)
/UART_TX: U1.21 (GPIO3/RXD), U2.26 (TXD)
/USB_D+: U2.4 (D+), U6.6 (I/O1)
/USB_D-: U2.5 (D-), U6.4 (I/O2)
/USB_DM_CON: J1.A7 (D-), J1.B7 (D-), U6.3 (I/O2)
/USB_DP_CON: J1.A6 (D+), J1.B6 (D+), U6.1 (I/O1)
/VBAT: Q3.3 (D), R20.1, SW3.1 (A)
/VBAT_RAW: C9.1, Q4.2 (S), SW3.2 (B), U3.3 (V_{BAT})
/VBAT_SENSE: C17.1, R20.2, R21.1, U1.2 (ADC)
/VBUS: C6.1, C7.1, C8.1, D1.2 (A), J1.A4 (VBUS), J1.A9 (VBUS), J1.B4 (VBUS), J1.B9 (VBUS), Q3.1 (G), R9.1, R12.1, R15.1, U2.7 (VREGIN), U3.4 (V_{DD}), U6.5 (VBUS)
/VBUS_SENSE: R12.2, R13.1, U2.8 (VBUS)
/VSYS: C10.1, C18.1, D1.1 (K), L1.1, Q3.2 (S), U4.1 (VIN), U4.3 (EN), U7.5 (IN)

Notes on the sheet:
MCU - ESP-12F (ESP8266)
Power Path + 3V3 LDO
Air Quality PCB
Air Sensor (BME688)
WiFi Mode Switch (SW4): POS.1 = OFF (GPIO12 low) — POS.2 = SPARSE, upload 1x/h (both inputs high) — POS.3 = CONTINUOUS (GPIO14 low). Read at boot with internal pull-ups (no external pull-ups: +3V3 stays live in deep sleep).
Power Flags
USB-UART Bridge (CP2102N)
USB-C Input + ESD
LiPo Charger (MCP73831)
Servo 5V Boost (MT3608)
Servo Output
